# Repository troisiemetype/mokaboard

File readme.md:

This is a board using RGB leds and soft pad buttons. It's inspired by Monome and Trellis from Adafruit.

This work is published under the terms of the GNU GPL v3 licence.

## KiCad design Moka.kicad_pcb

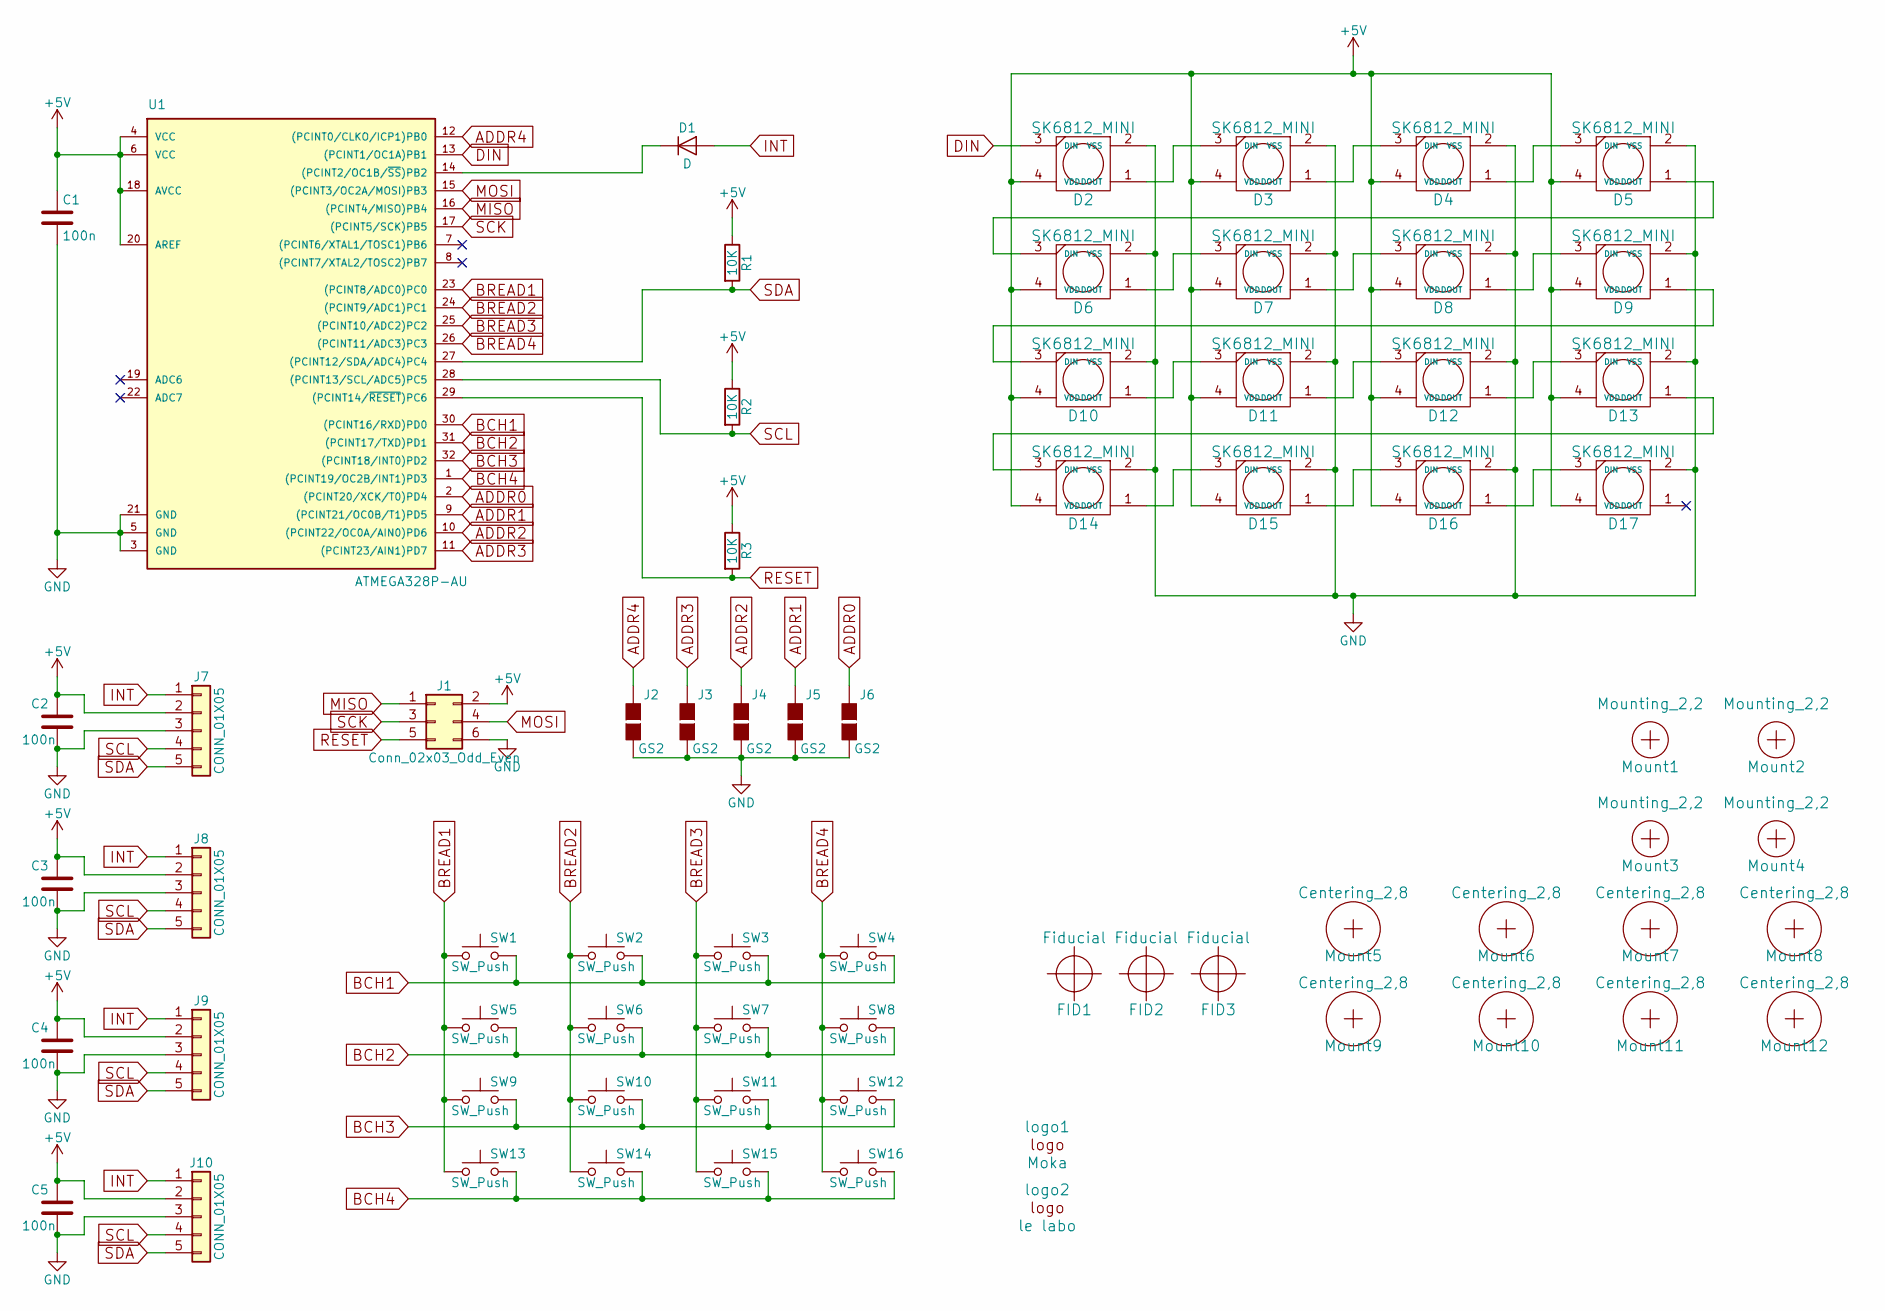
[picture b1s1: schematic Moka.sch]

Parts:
C1, C2, C3, C4, C5: 100n; C_0603
D1: D; D_SOD-123
D2, D3, D4, D5, D6, D7, D8, D9, D10, D11, D12, D13, D14, D15, D16, D17: SK6812_MINI; SK6812-mini
FID1, FID2, FID3: Fiducial; Fiducial_1mm_Dia_2.54mm_Outer_CopperTop
J1: Conn_02x03_Odd_Even; Pin_Header_Straight_2x03_Pitch2.54mm_SMD
J2, J3, J4, J5, J6: GS2
J7, J8, J9, J10: CONN_01X05; Connecteur_1x5_SMD
Mount1, Mount2, Mount3, Mount4: Mounting_2,2; MountingHole_2.2mm_M2
Mount5, Mount6, Mount7, Mount8, Mount9, Mount10, Mount11, Mount12: Centering_2,8; MountingHole_2.7mm_M2.5
R1, R2, R3: 10K; R_0603
SW1, SW2, SW3, SW4, SW5, SW6, SW7, SW8, SW9, SW10, SW11, SW12, SW13, SW14, SW15, SW16: SW_Push; Pad_30
U1: ATMEGA328P-AU; TQFP-32_7x7mm_Pitch0.8mm
logo1: Moka; Moka_25mm
logo2: le labo; Le_labo_20mm

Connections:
+5V: C1.1, C2.1, C3.1, C4.1, C5.1, D2.4 (VDD), D3.4 (VDD), D4.4 (VDD), D5.4 (VDD), D6.4 (VDD), D7.4 (VDD), D8.4 (VDD), D9.4 (VDD), D10.4 (VDD), D11.4 (VDD), D12.4 (VDD), D13.4 (VDD), D14.4 (VDD), D15.4 (VDD), D16.4 (VDD), D17.4 (VDD), J1.2, J7.2, J8.2, J9.2, J10.2, R1.1, R2.1, R3.1, U1.4 (VCC), U1.6 (VCC), U1.18 (AVCC), U1.20 (AREF)
ADDR0: J6.1 (G1), U1.2 ((PCINT20/XCK/T0)PD4)
ADDR1: J5.1 (G1), U1.9 ((PCINT21/OC0B/T1)PD5)
ADDR2: J4.1 (G1), U1.10 ((PCINT22/OC0A/AIN0)PD6)
ADDR3: J3.1 (G1), U1.11 ((PCINT23/AIN1)PD7)
ADDR4: J2.1 (G1), U1.12 ((PCINT0/CLKO/ICP1)PB0)
BCH1: SW1.2, SW2.2, SW3.2, SW4.2, U1.30 ((PCINT16/RXD)PD0)
BCH2: SW5.2, SW6.2, SW7.2, SW8.2, U1.31 ((PCINT17/TXD)PD1)
BCH3: SW9.2, SW10.2, SW11.2, SW12.2, U1.32 ((PCINT18/INT0)PD2)
BCH4: SW13.2, SW14.2, SW15.2, SW16.2, U1.1 ((PCINT19/OC2B/INT1)PD3)
BREAD1: SW1.1, SW5.1, SW9.1, SW13.1, U1.23 ((PCINT8/ADC0)PC0)
BREAD2: SW2.1, SW6.1, SW10.1, SW14.1, U1.24 ((PCINT9/ADC1)PC1)
BREAD3: SW3.1, SW7.1, SW11.1, SW15.1, U1.25 ((PCINT10/ADC2)PC2)
BREAD4: SW4.1, SW8.1, SW12.1, SW16.1, U1.26 ((PCINT11/ADC3)PC3)
DIN: D2.3 (DIN), U1.13 ((PCINT1/OC1A)PB1)
GND: C1.2, C2.2, C3.2, C4.2, C5.2, D2.2 (VSS), D3.2 (VSS), D4.2 (VSS), D5.2 (VSS), D6.2 (VSS), D7.2 (VSS), D8.2 (VSS), D9.2 (VSS), D10.2 (VSS), D11.2 (VSS), D12.2 (VSS), D13.2 (VSS), D14.2 (VSS), D15.2 (VSS), D16.2 (VSS), D17.2 (VSS), J1.6, J2.2 (G2), J3.2 (G2), J4.2 (G2), J5.2 (G2), J6.2 (G2), J7.3, J8.3, J9.3, J10.3, U1.3 (GND), U1.5 (GND), U1.21 (GND)
INT: D1.2 (A), J7.1, J8.1, J9.1, J10.1
MISO: J1.1, U1.16 ((PCINT4/MISO)PB4)
MOSI: J1.4, U1.15 ((PCINT3/OC2A/MOSI)PB3)
unnamed: D1.1 (K), U1.14 ((PCINT2/OC1B/~SS~)PB2)
unnamed: D2.1 (DOUT), D3.3 (DIN)
unnamed: D3.1 (DOUT), D4.3 (DIN)
unnamed: D4.1 (DOUT), D5.3 (DIN)
unnamed: D5.1 (DOUT), D6.3 (DIN)
unnamed: D6.1 (DOUT), D7.3 (DIN)
unnamed: D7.1 (DOUT), D8.3 (DIN)
unnamed: D8.1 (DOUT), D9.3 (DIN)
unnamed: D10.1 (DOUT), D11.3 (DIN)
unnamed: D9.1 (DOUT), D10.3 (DIN)
unnamed: D11.1 (DOUT), D12.3 (DIN)
unnamed: D12.1 (DOUT), D13.3 (DIN)
unnamed: D13.1 (DOUT), D14.3 (DIN)
unnamed: D14.1 (DOUT), D15.3 (DIN)
unnamed: D15.1 (DOUT), D16.3 (DIN)
unnamed: D16.1 (DOUT), D17.3 (DIN)
RESET: J1.5, R3.2, U1.29 ((PCINT14/~RESET~)PC6)
SCK: J1.3, U1.17 ((PCINT5/SCK)PB5)
SCL: J7.4, J8.4, J9.4, J10.4, R2.2, U1.28 ((PCINT13/SCL/ADC5)PC5)
SDA: J7.5, J8.5, J9.5, J10.5, R1.2, U1.27 ((PCINT12/SDA/ADC4)PC4)

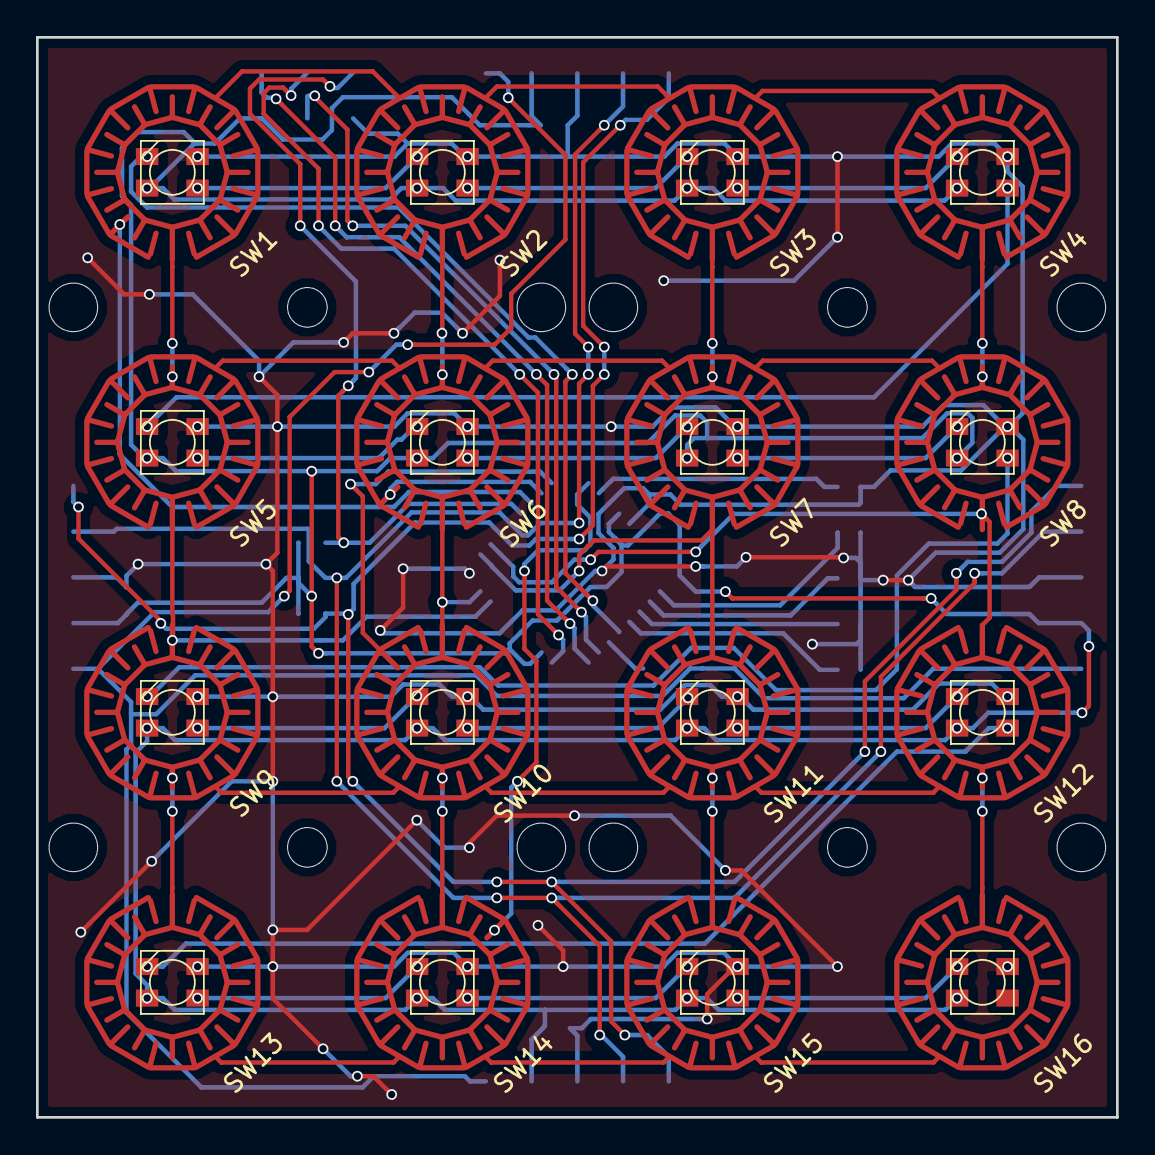
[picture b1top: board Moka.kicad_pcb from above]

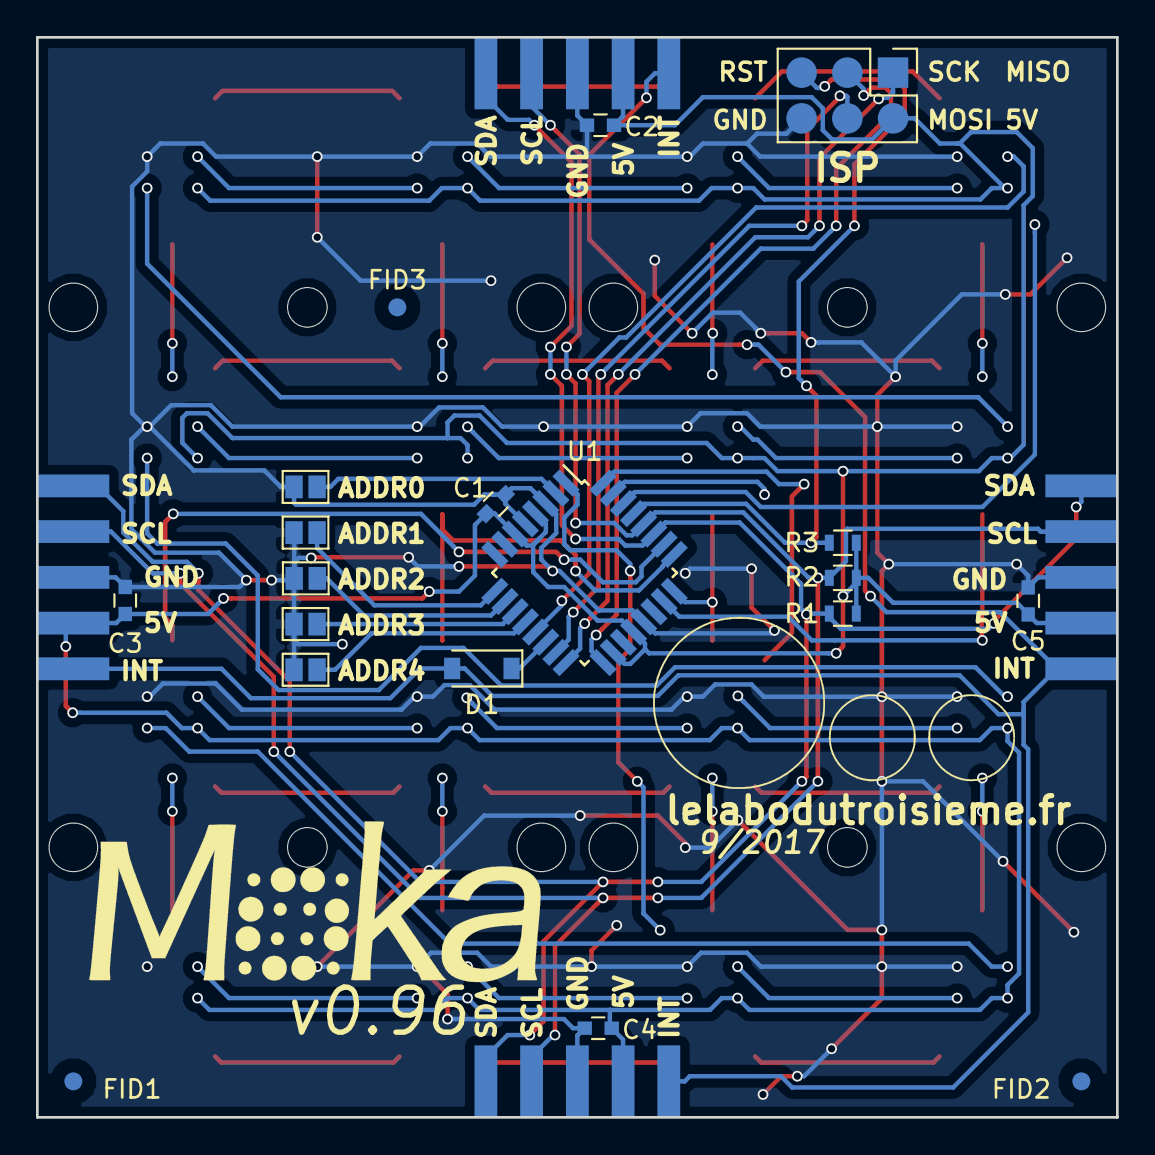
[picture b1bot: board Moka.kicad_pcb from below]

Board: 2 copper layers, 60.0 x 60.0 mm, 69 parts (25 on the bottom side), 39 nets.

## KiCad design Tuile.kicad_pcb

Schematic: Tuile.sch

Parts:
C1, C2, C3, C4, C5: 100n; C_0603
D1, D2, D3, D4, D5, D6, D7, D8, D9, D10, D11, D12, D13, D14, D15, D16: Led_3535_addr; SK6812-mini
FID1, FID2, FID3: Fiducial; Fiducial_1mm_Dia_2.54mm_Outer_CopperTop
J1: CONN_02X03; Pin_Header_Straight_2x03_Pitch2.54mm_SMD
J2, J3, J4, J5, J6: GS2
J7, J8, J9, J10: CONN_01X05; Connecteur_1x5_SMD
Mount1, Mount2, Mount3, Mount4: Mounting_2,2; MountingHole_2.2mm_M2
Mount5, Mount6, Mount7, Mount8, Mount9, Mount10, Mount11, Mount12: Centering_2,8; MountingHole_2.7mm_M2.5
R1, R2, R3: 10K; R_0603
SW1, SW2, SW3, SW4, SW5, SW6, SW7, SW8, SW9, SW10, SW11, SW12, SW13, SW14, SW15, SW16: SW_Push; Pad_30
U1: ATMEGA328P-AU; TQFP-32_7x7mm_Pitch0.8mm

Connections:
+5V: C1.1, C2.1, C3.1, C4.1, C5.1, D1.3, D2.3, D3.3, D4.3, D5.3, D6.3, D7.3, D8.3, D9.3, D10.3, D11.3, D12.3, D13.3, D14.3, D15.3, D16.3, J1.2, J7.2, J8.2, J9.2, J10.2, R1.1, R2.1, R3.1, U1.4 (VCC), U1.6 (VCC), U1.18 (AVCC), U1.20 (AREF)
ADDR0: J6.1 (G1), U1.12 ((PCINT0/CLKO/ICP1)PB0)
ADDR1: J5.1 (G1), U1.13 ((PCINT1/OC1A)PB1)
ADDR2: J4.1 (G1), U1.14 ((PCINT2/OC1B/~SS~)PB2)
ADDR3: J3.1 (G1), U1.30 ((PCINT16/RXD)PD0)
ADDR4: J2.1 (G1), U1.31 ((PCINT17/TXD)PD1)
BIN1: SW1.2, SW2.2, SW3.2, SW4.2, U1.23 ((PCINT8/ADC0)PC0)
BIN2: SW5.2, SW6.2, SW7.2, SW8.2, U1.24 ((PCINT9/ADC1)PC1)
BIN3: SW9.2, SW10.2, SW11.2, SW12.2, U1.25 ((PCINT10/ADC2)PC2)
BIN4: SW13.2, SW14.2, SW15.2, SW16.2, U1.26 ((PCINT11/ADC3)PC3)
BOUT1: SW1.1, SW5.1, SW9.1, SW13.1, U1.2 ((PCINT20/XCK/T0)PD4)
BOUT2: SW2.1, SW6.1, SW10.1, SW14.1, U1.9 ((PCINT21/OC0B/T1)PD5)
BOUT3: SW3.1, SW7.1, SW11.1, SW15.1, U1.10 ((PCINT22/OC0A/AIN0)PD6)
BOUT4: SW4.1, SW8.1, SW12.1, SW16.1, U1.11 ((PCINT23/AIN1)PD7)
DIN: D1.2, U1.1 ((PCINT19/OC2B/INT1)PD3)
GND: C1.2, C2.2, C3.2, C4.2, C5.2, D1.1, D2.1, D3.1, D4.1, D5.1, D6.1, D7.1, D8.1, D9.1, D10.1, D11.1, D12.1, D13.1, D14.1, D15.1, D16.1, J1.6, J2.2 (G2), J3.2 (G2), J4.2 (G2), J5.2 (G2), J6.2 (G2), J7.3, J8.3, J9.3, J10.3, U1.3 (GND), U1.5 (GND), U1.21 (GND)
INT: J7.1, J8.1, J9.1, J10.1, U1.32 ((PCINT18/INT0)PD2)
MISO: J1.1, U1.16 ((PCINT4/MISO)PB4)
MOSI: J1.4, U1.15 ((PCINT3/OC2A/MOSI)PB3)
unnamed: D1.4, D2.2
unnamed: D2.4, D3.2
unnamed: D3.4, D4.2
unnamed: D4.4, D5.2
unnamed: D5.4, D6.2
unnamed: D6.4, D7.2
unnamed: D7.4, D8.2
unnamed: D8.4, D9.2
unnamed: D9.4, D10.2
unnamed: D10.4, D11.2
unnamed: D11.4, D12.2
unnamed: D12.4, D13.2
unnamed: D13.4, D14.2
unnamed: D14.4, D15.2
unnamed: D15.4, D16.2
RESET: J1.5, R3.2, U1.29 ((PCINT14/~RESET~)PC6)
SCK: J1.3, U1.17 ((PCINT5/SCK)PB5)
SCL: J7.4, J8.4, J9.4, J10.4, R2.2, U1.28 ((PCINT13/SCL/ADC5)PC5)
SDA: J7.5, J8.5, J9.5, J10.5, R1.2, U1.27 ((PCINT12/SDA/ADC4)PC4)

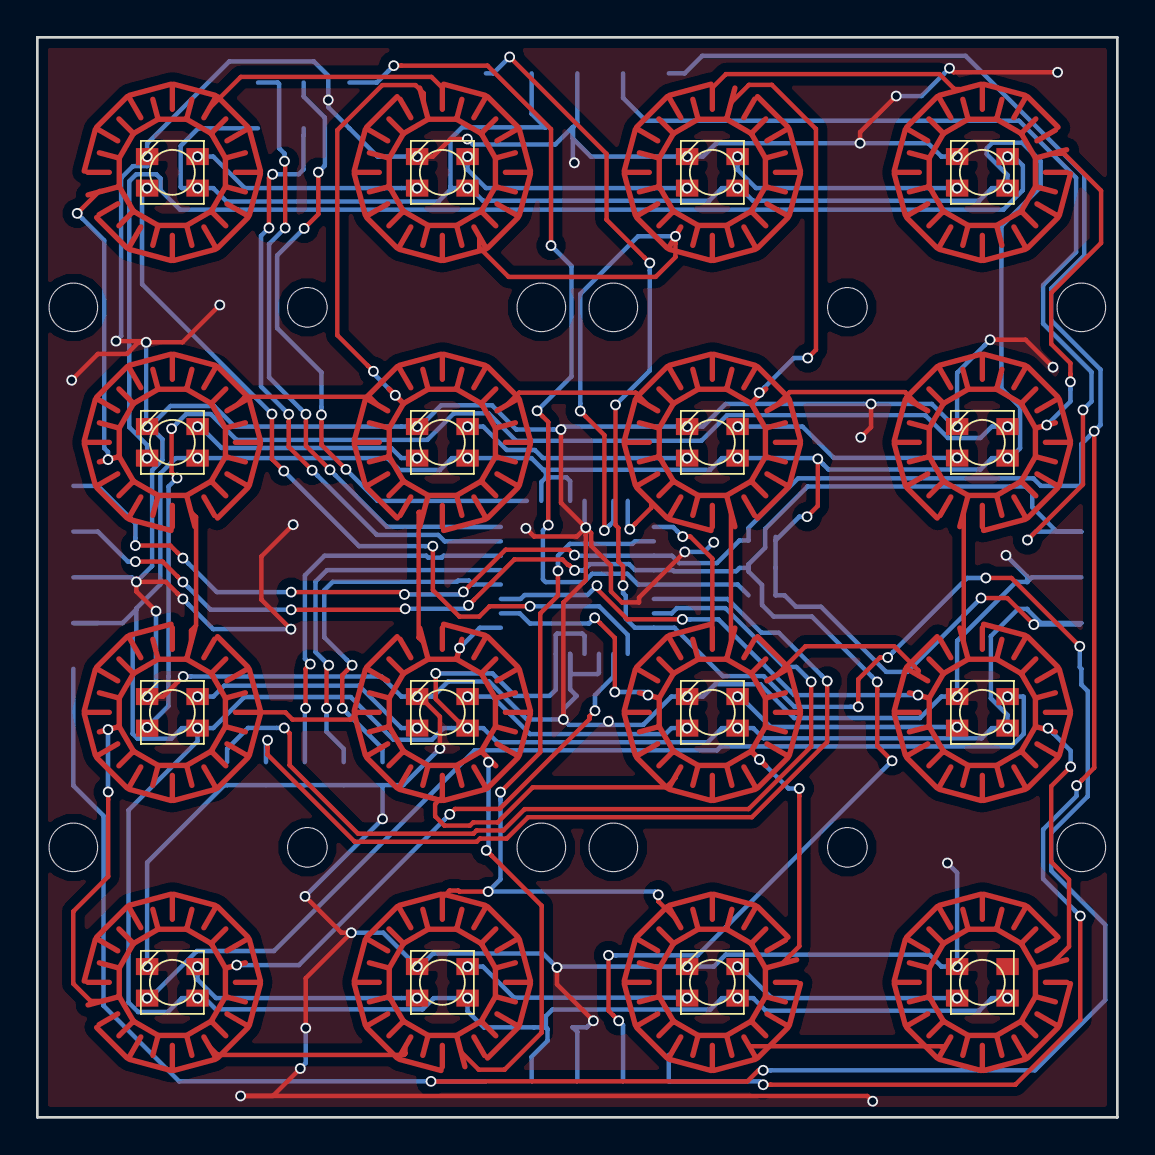
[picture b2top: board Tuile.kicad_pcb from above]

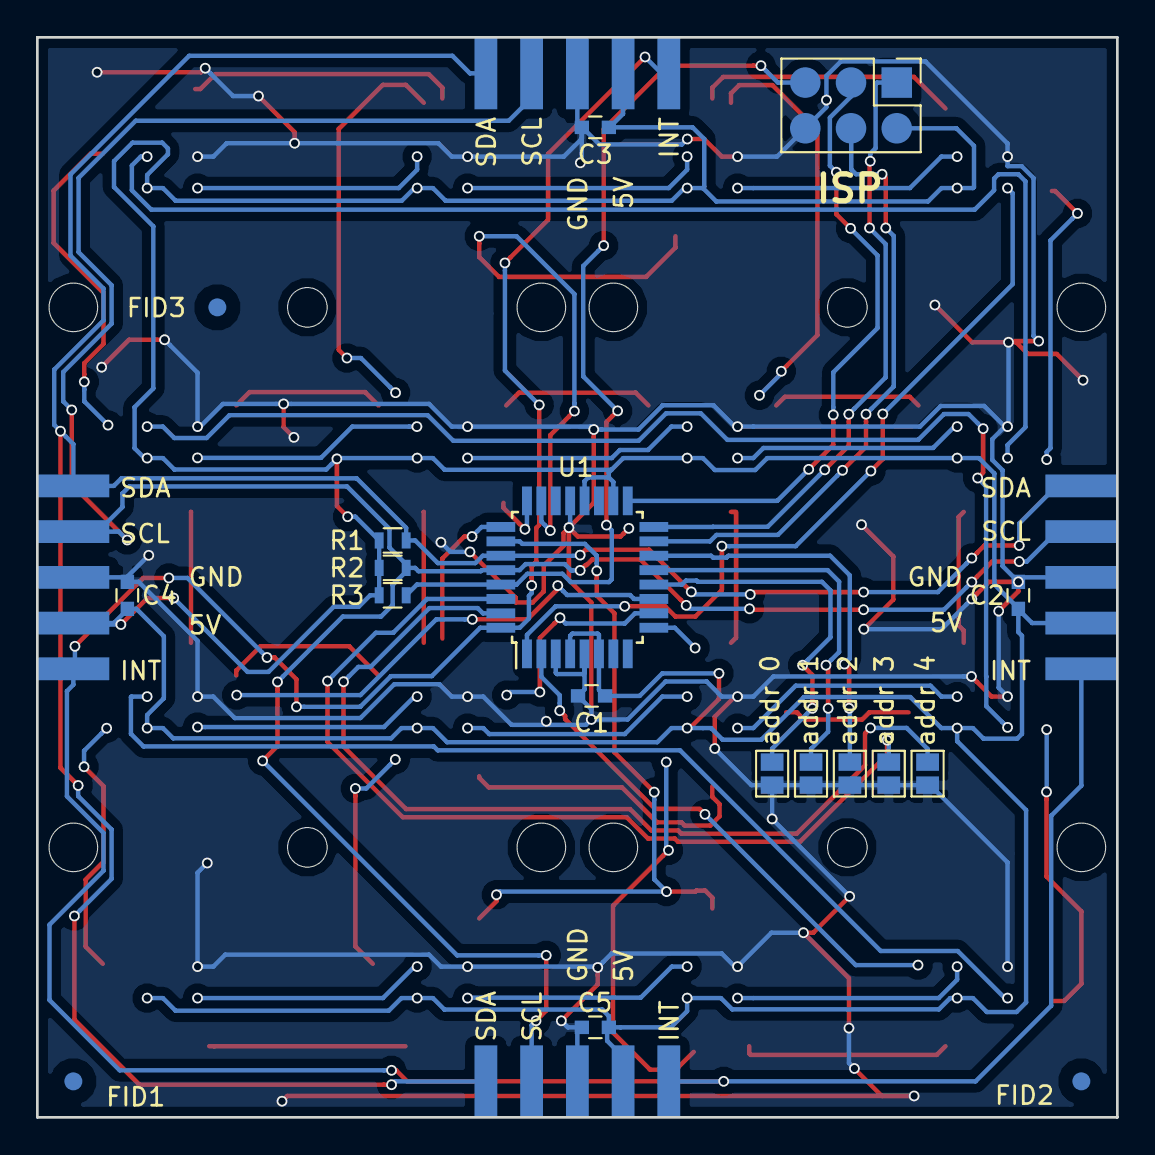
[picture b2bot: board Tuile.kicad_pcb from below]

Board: 2 copper layers, 60.0 x 60.0 mm, 66 parts (22 on the bottom side), 38 nets.

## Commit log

2017-06-23 Initial commit.
2017-06-23 Add readme.
2017-06-25 Design ok, first prototype batch ordered.
2017-09-19 v0.95 ready for fabrication.
2017-09-29 Modified diode footprint on INT.
2017-09-29 Added fabrication files.
2017-09-29 Added schematic.
2018-01-12 Added missing via on last led raw GND.
2018-01-12 Fixed missing via on last led GND.
